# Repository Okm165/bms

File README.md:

# Battery Management System
## BMS device firmware, harware and client software

Sections:

- client - external software to contact firmware endpoints
- firmware - operating system and functionalities on hardware device
- hardware - physical project of bms

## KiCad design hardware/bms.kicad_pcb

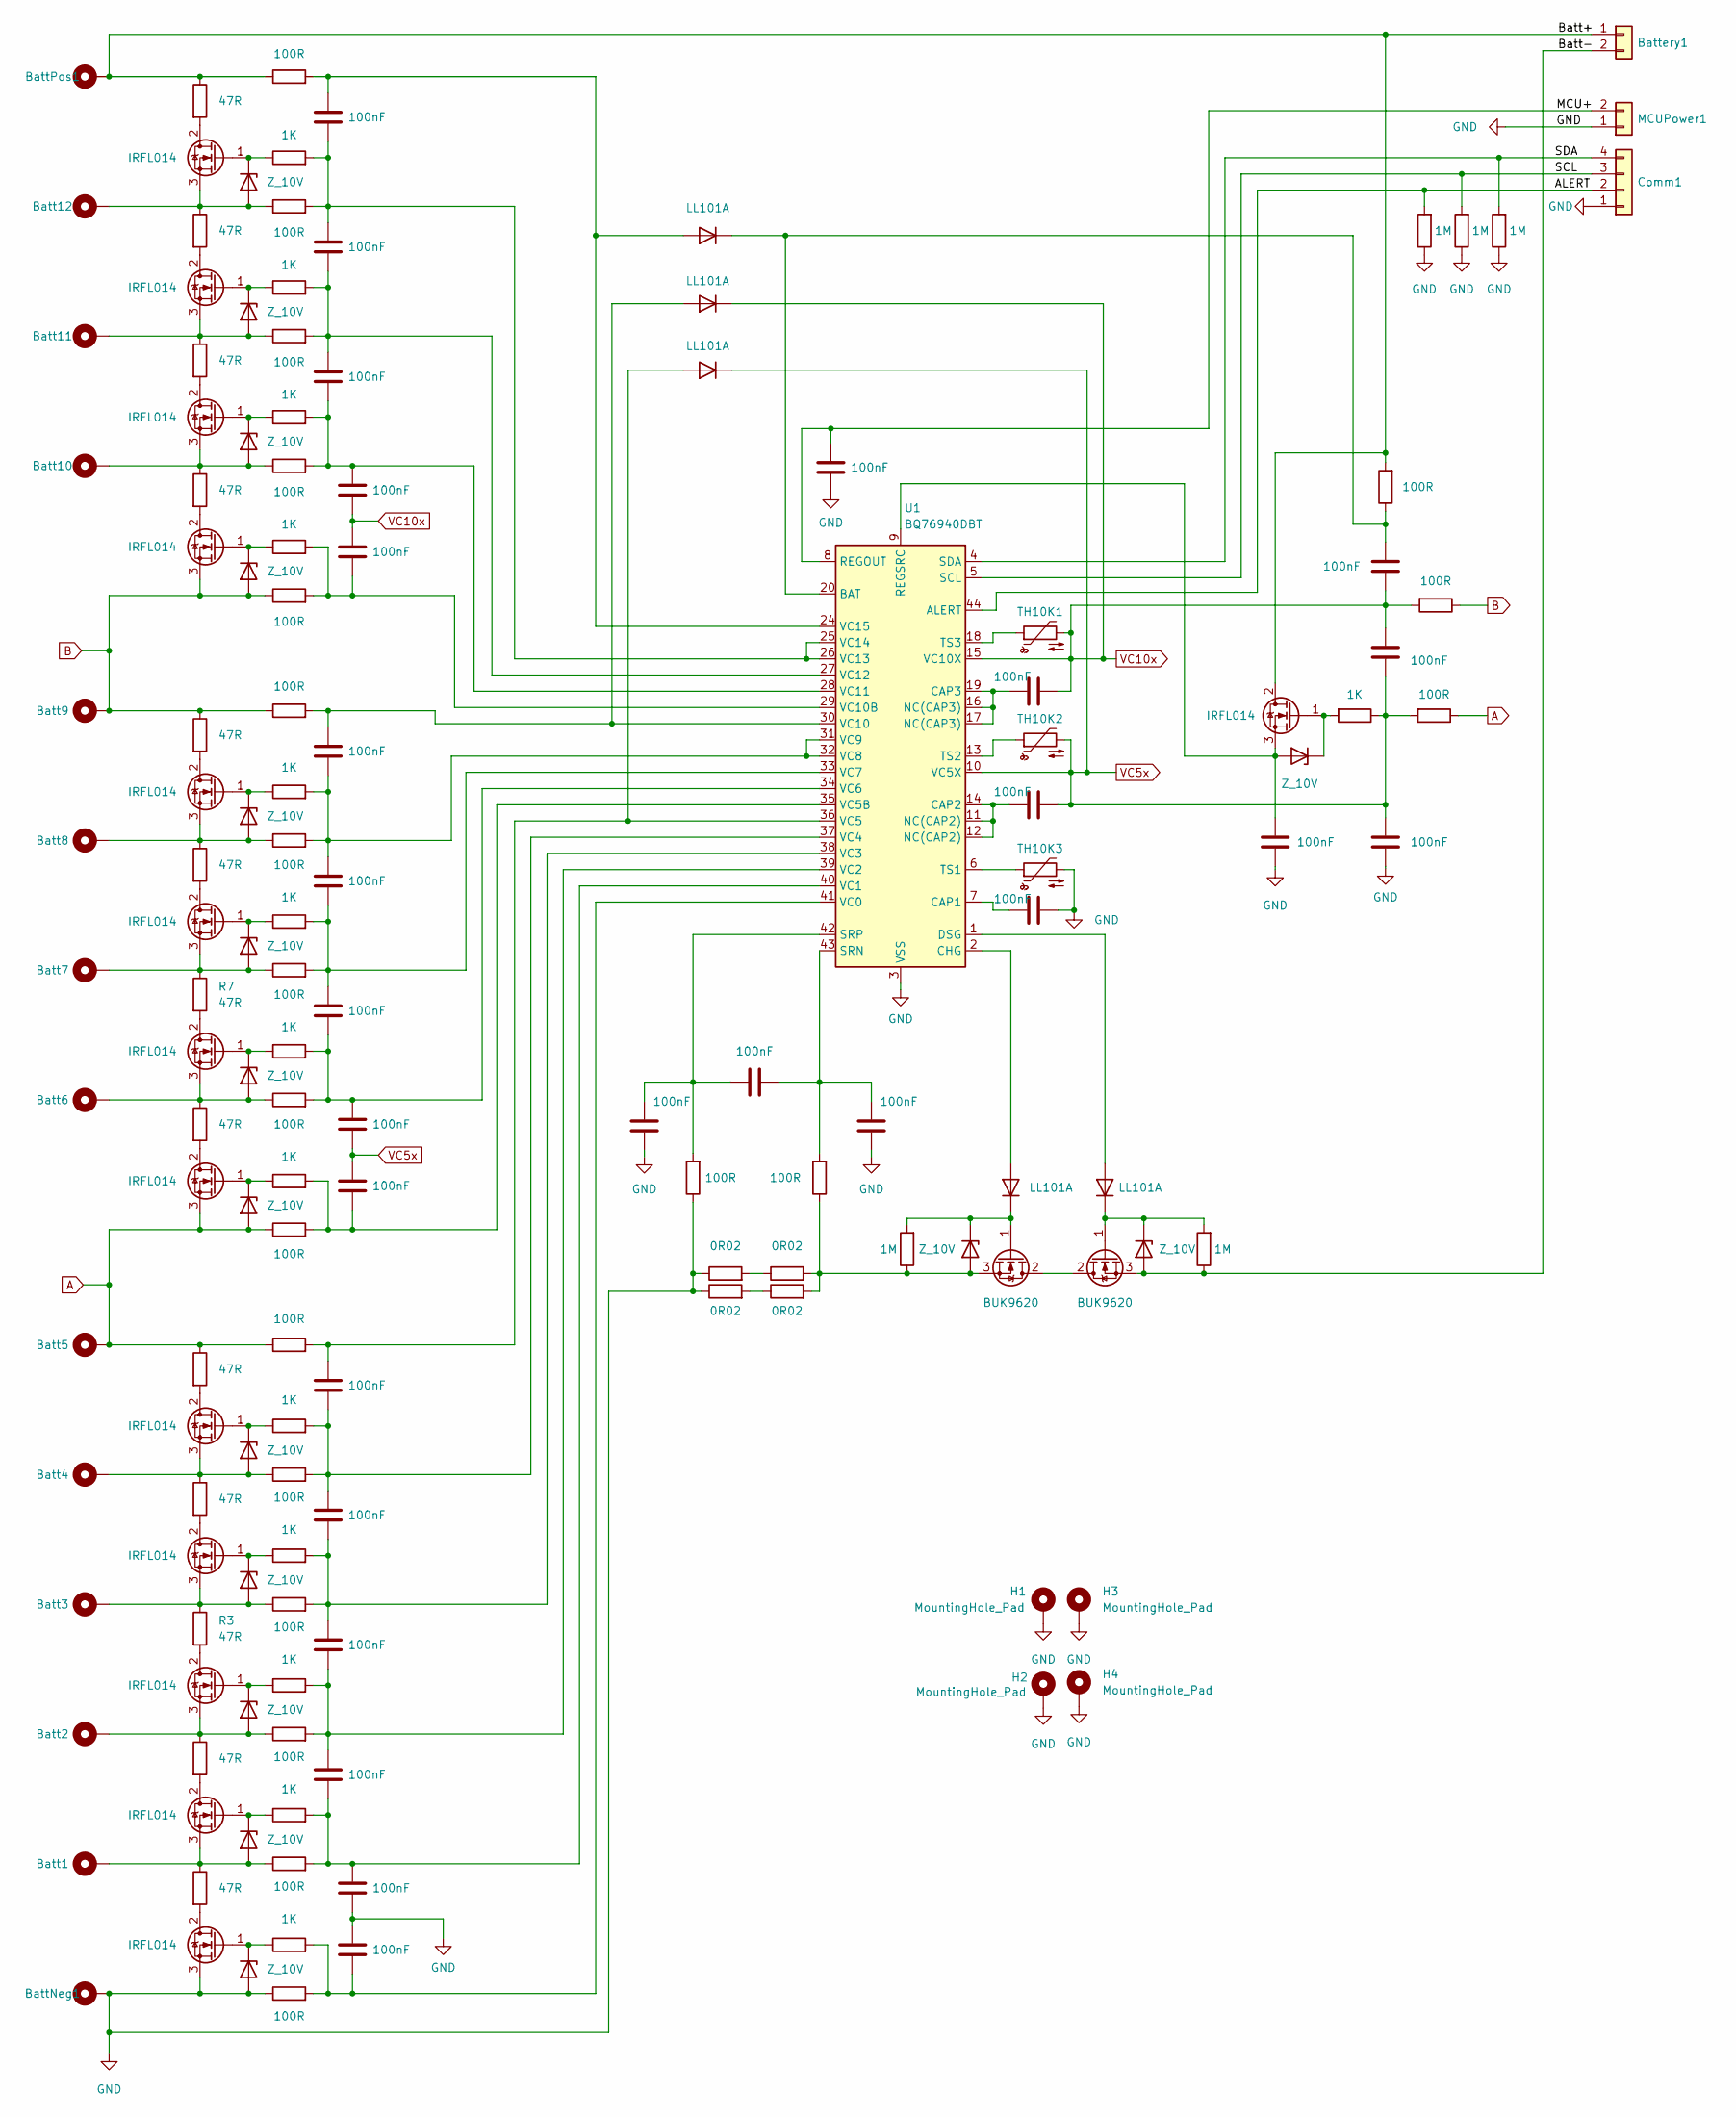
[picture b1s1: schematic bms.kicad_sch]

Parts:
Batt1, Batt2, Batt3, Batt4, Batt5, Batt6, Batt7, Batt8, Batt9, Batt10, Batt11, Batt12: MountingHole_Pad; TestPoint_Pad_4.0x4.0mm
BattNeg1: MountingHole_Pad; TestPoint_Pad_4.0x4.0mm
BattPos1: MountingHole_Pad; TestPoint_Pad_4.0x4.0mm
Battery1: Conn_01x02; PhoenixContact_MCV_1,5_2-G-5.08_1x02_P5.08mm_Vertical
C1, C2, C3, C4, C5, C6, C7, C8, C9, C10, C11, C12, C13, C14, C15, C16, C17, C18, C19, C20, C21, C22, C23, C24, C25, C26, C27: 100nF; C_1206_3216Metric
Comm1: Conn_01x04; PinHeader_1x04_P2.00mm_Vertical
D1, D2, D3, D4, D5, D6, D7, D8, D9, D10, D11, D12, D13, D16, D19, D20: Z_10V; D_MiniMELF
D14, D15, D17, D18, D21: LL101A; D_MiniMELF
H1, H2, H3, H4: MountingHole_Pad; MountingHole_3.2mm_M3_Pad_Via
MCUPower1: Conn_01x02; PinHeader_1x02_P2.00mm_Vertical
Q1, Q2, Q3, Q4, Q5, Q6, Q7, Q8, Q9, Q10, Q11, Q12, Q13, Q16: IRFL014; SOT-223-3_TabPin2
Q14, Q15: BUK9620; TO-263-2
R1, R2, R3, R4, R5, R6, R7, R8, R9, R10, R11, R12, R13: 47R; R_2512_6332Metric
R14, R16, R18, R20, R22, R23, R25, R27, R29, R31, R32, R34, R36, R38, R40, R42, R43, R44, R48, R52, R53: 100R; R_0805_2012Metric
R15, R17, R19, R21, R24, R26, R28, R30, R33, R35, R37, R39, R41, R47: 1K; R_0805_2012Metric
R45, R46, R49, R50, R51: 1M; R_0805_2012Metric
RSense1, RSense2, RSense3, RSense4: 0R02; R_2010_5025Metric
TH10K1, TH10K2, TH10K3: Thermistor_NTC; C_Disc_D5.0mm_W2.5mm_P2.50mm
U1: BQ76940DBT; TSSOP-44_4.4x11.2mm_P0.5mm

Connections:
/ALERT: Comm1.2, R49.2, U1.44 (ALERT)
/Batt+: BattPos1.1, Battery1.1, Q16.2 (D), R13.1, R14.1, R48.2
/Batt-: Battery1.2, D19.2 (A), Q15.3 (S), R46.1
/MCU+: C19.2, MCUPower1.2, U1.8 (REGOUT)
/SCL: Comm1.3, R50.2, U1.5 (SCL)
/SDA: Comm1.4, R51.2, U1.4 (SDA)
A: Batt5.1, D6.2 (A), Q6.3 (S), R5.1, R31.1, R32.1, R52.1
B: Batt9.1, D10.2 (A), Q10.3 (S), R9.1, R22.1, R23.1, R53.1
GND: BattNeg1.1, C15.2, C16.1, C17.1, C19.1, C20.1, C23.2, C24.1, C27.1, Comm1.1, D1.2 (A), H1.1, H2.1, H3.1, H4.1, MCUPower1.1, Q1.3 (S), R42.1, R43.1, R49.1, R50.1, R51.1, RSense1.1, RSense2.1, TH10K3.2, U1.3 (VSS)
unnamed: Batt1.1, D2.2 (A), Q2.3 (S), R1.1, R40.1
unnamed: Batt2.1, D3.2 (A), Q3.3 (S), R2.1, R38.1
unnamed: Batt3.1, D4.2 (A), Q4.3 (S), R3.1, R36.1
unnamed: Batt4.1, D5.2 (A), Q5.3 (S), R4.1, R34.1
unnamed: Batt6.1, D7.2 (A), Q7.3 (S), R6.1, R29.1
unnamed: Batt7.1, D8.2 (A), Q8.3 (S), R7.1, R27.1
unnamed: Batt8.1, D9.2 (A), Q9.3 (S), R8.1, R25.1
unnamed: Batt10.1, D11.2 (A), Q11.3 (S), R10.1, R20.1
unnamed: Batt11.1, D12.2 (A), Q12.3 (S), R11.1, R18.1
unnamed: Batt12.1, D13.2 (A), Q13.3 (S), R12.1, R16.1
unnamed: C1.1, D21.2 (A), R14.2, U1.24 (VC15)
unnamed: C1.2, C2.1, R15.2, R16.2, U1.25 (VC14), U1.26 (VC13)
unnamed: C2.2, C3.1, R17.2, R18.2, U1.27 (VC12)
unnamed: C4.1, D14.2 (A), R23.2, U1.30 (VC10)
unnamed: C4.2, C5.1, R24.2, R25.2, U1.31 (VC9), U1.32 (VC8)
unnamed: C5.2, C6.1, R26.2, R27.2, U1.33 (VC7)
unnamed: C7.1, D15.2 (A), R32.2, U1.36 (VC5)
unnamed: C7.2, C8.1, R33.2, R34.2, U1.37 (VC4)
unnamed: C8.2, C9.1, R35.2, R36.2, U1.38 (VC3)
unnamed: C9.2, C10.1, R37.2, R38.2, U1.39 (VC2)
unnamed: C10.2, C15.1, R39.2, R40.2, U1.40 (VC1)
unnamed: C3.2, C11.1, R19.2, R20.2, U1.28 (VC11)
unnamed: C12.2, R21.2, R22.2, U1.29 (VC10B)
unnamed: C6.2, C13.1, R28.2, R29.2, U1.34 (VC6)
unnamed: C14.2, R30.2, R31.2, U1.35 (VC5B)
unnamed: C16.2, R41.2, R42.2, U1.41 (VC0)
unnamed: C17.2, C18.2, R43.2, U1.42 (SRP)
unnamed: C18.1, C20.2, R44.2, U1.43 (SRN)
unnamed: C21.1, U1.16 (NC(CAP3)), U1.17 (NC(CAP3)), U1.19 (CAP3)
unnamed: C22.1, U1.11 (NC(CAP2)), U1.12 (NC(CAP2)), U1.14 (CAP2)
unnamed: C23.1, U1.7 (CAP1)
unnamed: C24.2, D20.2 (A), Q16.3 (S), U1.9 (REGSRC)
unnamed: C25.2, D21.1 (K), R48.1, U1.20 (BAT)
unnamed: D1.1 (K), Q1.1 (G), R41.1
unnamed: D2.1 (K), Q2.1 (G), R39.1
unnamed: D3.1 (K), Q3.1 (G), R37.1
unnamed: D4.1 (K), Q4.1 (G), R35.1
unnamed: D5.1 (K), Q5.1 (G), R33.1
unnamed: D6.1 (K), Q6.1 (G), R30.1
unnamed: D7.1 (K), Q7.1 (G), R28.1
unnamed: D8.1 (K), Q8.1 (G), R26.1
unnamed: D9.1 (K), Q9.1 (G), R24.1
unnamed: D10.1 (K), Q10.1 (G), R21.1
unnamed: D11.1 (K), Q11.1 (G), R19.1
unnamed: D12.1 (K), Q12.1 (G), R17.1
unnamed: D13.1 (K), Q13.1 (G), R15.1
unnamed: D16.1 (K), D17.1 (K), Q14.1 (G), R45.2
unnamed: D16.2 (A), Q14.3 (S), R44.1, R45.1, RSense3.2, RSense4.2
unnamed: D17.2 (A), U1.2 (CHG)
unnamed: D18.1 (K), D19.1 (K), Q15.1 (G), R46.2
unnamed: D18.2 (A), U1.1 (DSG)
unnamed: D20.1 (K), Q16.1 (G), R47.2
unnamed: Q1.2 (D), R1.2
unnamed: Q2.2 (D), R2.2
unnamed: Q3.2 (D), R3.2
unnamed: Q4.2 (D), R4.2
unnamed: Q5.2 (D), R5.2
unnamed: Q6.2 (D), R6.2
unnamed: Q7.2 (D), R7.2
unnamed: Q8.2 (D), R8.2
unnamed: Q9.2 (D), R9.2
unnamed: Q10.2 (D), R10.2
unnamed: Q11.2 (D), R11.2
unnamed: Q12.2 (D), R12.2
unnamed: Q13.2 (D), R13.2
unnamed: Q14.2 (D), Q15.2 (D)
unnamed: RSense1.2, RSense3.1
unnamed: RSense2.2, RSense4.1
unnamed: TH10K1.1, U1.18 (TS3)
unnamed: TH10K2.1, U1.13 (TS2)
unnamed: TH10K3.1, U1.6 (TS1)
VC5x: C13.2, C14.1, C22.2, C26.1, C27.2, D15.1 (K), R47.1, R52.2, TH10K2.2, U1.10 (VC5X)
VC10x: C11.2, C12.1, C21.2, C25.1, C26.2, D14.1 (K), R53.2, TH10K1.2, U1.15 (VC10X)

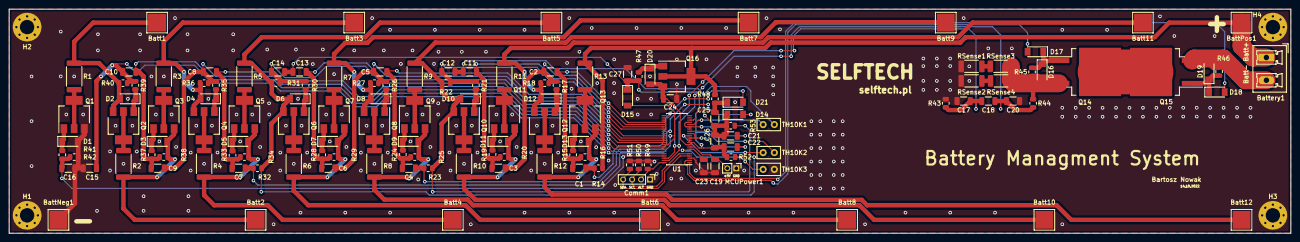
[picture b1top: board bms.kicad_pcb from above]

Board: 2 copper layers, 286.0 x 50.0 mm, 146 parts (0 on the bottom side), 82 nets.

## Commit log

2022-12-25 working base
2022-12-25 working tcp server
2022-12-25 makefile upgrade
2022-12-25 formatting and linting
2022-12-25 clang-format
2022-12-26 first cpp
2022-12-26 tcp server class
2022-12-26 multiple connections poor example
2022-12-27 tcp_server multiple connections
2022-12-27 simple echo server impl
2022-12-30 interface and basic functionalities
2022-12-30 order
2022-12-30 refactor
2022-12-30 del target
2022-12-30 readme
2023-01-02 bq driver primitives
2023-01-02 bq datasheet
2023-01-02 bms supervisor init
2023-01-02 matrixlib
